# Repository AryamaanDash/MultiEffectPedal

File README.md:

# MultiEffectPedal

## Description

Multi-effect guitar pedal firmware and a custom KiCad PCB for the Daisy Seed.
The firmware runs distortion, stereo reverb, delay, and flanger effects at the
Daisy audio sample rate, with a footswitch for cycling through the effects.

## Firmware architecture

```text
src/main.cpp             Hardware composition and application entry point
src/AudioEngine.cpp      Real-time block processing and output limiting
src/EffectManager.cpp    Effect ownership-independent routing and mode changes
src/PedalControls.cpp    Foreground switch scanning and LED state
src/effects/             Individual DSP effect adapters
include/                 Public interfaces and shared audio types
```

Every effect implements the `EffectProcessor` interface:

```cpp
virtual void Init(float sample_rate) = 0;
virtual void SetParameters(const EffectParameters& parameters) = 0;
virtual StereoFrame Process(float input) = 0;
```

Effect parameters use normalized values from 0 to 1. Each adapter maps those
values to the range expected by its DaisySP processor. Mode changes are sent
from the foreground loop through an atomic request and applied by the audio
engine at the next block boundary.

The reverb and one-second delay buffers remain in external SDRAM. Effect
objects and the manager are statically allocated; audio processing performs no
dynamic allocation.

## Building

This project expects `libDaisy` and `DaisySP` to be available at the paths in
the `Makefile`.

```sh
make
```

To add an effect, implement `EffectProcessor`, register the instance with
`EffectManager`, and add its source file to `CPP_SOURCES` in the `Makefile`.

## Tools

- Daisy Seed and libDaisy
- DaisySP and DaisySP-LGPL
- KiCad PCB and schematic design

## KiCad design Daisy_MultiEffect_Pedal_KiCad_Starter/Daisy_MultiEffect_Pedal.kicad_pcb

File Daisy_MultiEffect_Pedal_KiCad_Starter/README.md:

# Daisy Seed Multi-Effect Guitar Pedal KiCad Starter

Files:
- Daisy_MultiEffect_Pedal.kicad_sch
- Daisy_MultiEffect_Pedal.kicad_pcb
- Daisy_MultiEffect_Pedal.kicad_pro

Important:
- This is a starter schematic/PCB template, not a production-ready board.
- Open in KiCad, verify every symbol, footprint, and pinout.
- Run ERC and DRC before fabrication.
- USB power is assumed for the prototype.
- Do not connect 9V, VIN, or 5V to Daisy ADC pins or +3V3A.
- Your current C++ writes mono to both output channels but this PCB routes only AUDIO OUT L to the mono output jack.
- RV5 is wired as a passive output volume control, so the single potentiometer does something with the current firmware.
- RV1-RV4 are optional future ADC control headers. Do not populate them unless you also update the firmware to read ADC values.

Key nets:
- D9_SWITCH: momentary footswitch to GND
- AUDIO_IN_L: buffered guitar input into Daisy audio input left
- AUDIO_OUT_L: Daisy audio output left into output buffer
- VREF_1V65: half-supply bias for the single-supply op-amp sections
- OUT_LEVEL_IN: AC-coupled signal into RV5 volume lug 3
- OUT_JACK_TIP: RV5 wiper to the output jack tip
- +3V3A: Daisy analog 3.3V rail
- GND: AGND and DGND tied together

Build wiring:
- Put the MCP6002 in an 8-pin DIP socket at U1. Pin 1 is the notched/dot end.
- Wire the input jack tip/sleeve to J1 pad 1/pad 2.
- Wire the output jack tip/sleeve to J2 pad 1/pad 2.
- Wire the momentary footswitch to SW1 pad 1 and pad 2.
- Wire the volume pot to RV5: pad 1 = CCW/GND, pad 2 = wiper/output, pad 3 = CW/input from output coupling capacitor.
- Mount RV1-RV4 only if you add ADC support in firmware later.

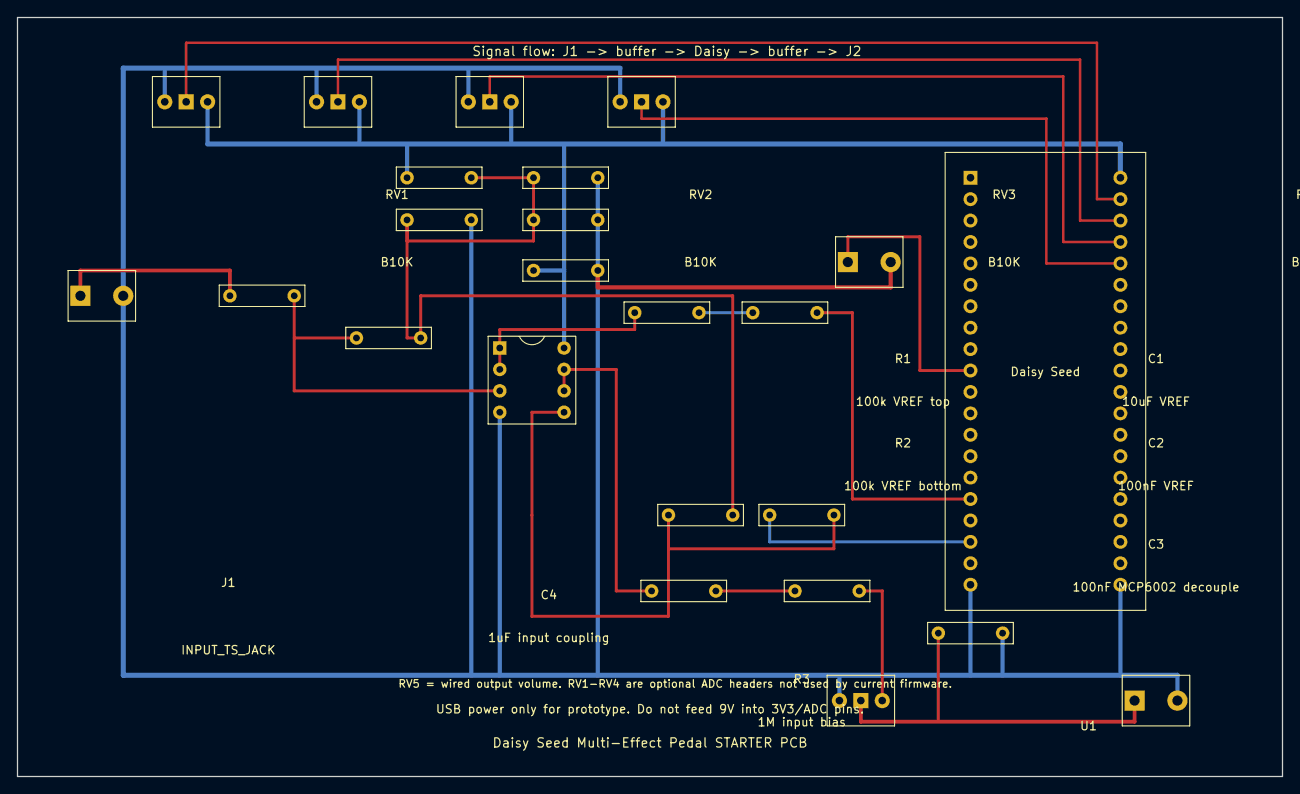
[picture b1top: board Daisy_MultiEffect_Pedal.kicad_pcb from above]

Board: 2 copper layers, 150.0 x 90.0 mm, 24 parts (0 on the bottom side), 19 nets.

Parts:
C1: 10uF VREF; TH_2Pin_7p62
C2: 100nF VREF; TH_2Pin_7p62
C3: 100nF MCP6002 decouple; TH_2Pin_7p62
C4: 1uF input coupling; TH_2Pin_7p62
C5: 1uF to Daisy In; TH_2Pin_7p62
C6: 1uF from Daisy Out; TH_2Pin_7p62
C7: 10uF output coupling; TH_2Pin_7p62
J1: INPUT_TS_JACK; Jack_or_Switch_2Pin
J2: OUTPUT_TS_JACK; Jack_or_Switch_2Pin
R1: 100k VREF top; TH_2Pin_7p62
R2: 100k VREF bottom; TH_2Pin_7p62
R3: 1M input bias; TH_2Pin_7p62
R4: 100R; TH_2Pin_7p62
R5: 100k out bias; TH_2Pin_7p62
R6: 100R out iso; TH_2Pin_7p62
R7: 100k output pulldown; TH_2Pin_7p62
RV1, RV2, RV3, RV4: B10K; Pot_3Pin_B10K_Wired
RV5: B10K volume; Pot_3Pin_B10K_Wired
SW1: MOMENTARY_MODE_SWITCH; Jack_or_Switch_2Pin
U1: MCP6002-I/P; DIP-8_W7.62mm
U2: Daisy Seed socket / 2x20; Daisy_Seed_2x20_Socket

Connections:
+3V3A: C3.1, R1.1, RV1.3 (CW/3V3A), RV2.3 (CW/3V3A), RV3.3 (CW/3V3A), RV4.3 (CW/3V3A), U1.8, U2.21 (PIN21)
AUDIO_IN_L: C5.2, U2.16 (PIN16)
AUDIO_OUT_L: C6.1, U2.18 (PIN18)
BUF_IN_OUT: R4.1, U1.1, U1.2
BUF_TO_DAISY_C: C5.1, R4.2
D9_SWITCH: SW1.1 (TIP/SW1), U2.10 (PIN10)
GND: C1.2, C2.2, C3.2, J1.2 (SLEEVE/SW2), J2.2 (SLEEVE/SW2), R2.2, R7.2, RV1.1 (CCW/GND), RV2.1 (CCW/GND), RV3.1 (CCW/GND), RV4.1 (CCW/GND), RV5.1 (CCW/GND), SW1.2 (SLEEVE/SW2), U1.4, U2.20 (PIN20), U2.40 (PIN40)
INPUT_NODE: C4.2, R3.1, U1.3
IN_JACK_TIP: C4.1, J1.1 (TIP/SW1)
OUT_BUF_INPUT: C6.2, R5.1, U1.5
OUT_BUF_OUT: R6.1, U1.6, U1.7
OUT_CAP_IN: C7.1, R6.2
OUT_JACK_TIP: J2.1 (TIP/SW1), R7.1, RV5.2 (WIPER)
OUT_LEVEL_IN: C7.2, RV5.3 (CW/LEVEL_IN)
POT1_A0_D15: RV1.2 (WIPER), U2.22 (PIN22)
POT2_A1_D16: RV2.2 (WIPER), U2.23 (PIN23)
POT3_A2_D17: RV3.2 (WIPER), U2.24 (PIN24)
POT4_A3_D18: RV4.2 (WIPER), U2.25 (PIN25)
VREF_1V65: C1.1, C2.1, R1.2, R2.1, R3.2, R5.2

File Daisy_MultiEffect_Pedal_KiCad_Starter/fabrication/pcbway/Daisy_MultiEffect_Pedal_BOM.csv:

"Refs","Value","Footprint","Qty","DNP"
"C1","10uF VREF bulk","Custom:TH_2Pin_7p62","1",""
"C2","100nF VREF bypass","Custom:TH_2Pin_7p62","1",""
"C3","100nF op-amp decouple","Custom:TH_2Pin_7p62","1",""
"C4","1uF input coupling","Custom:TH_2Pin_7p62","1",""
"C5","1uF into Daisy","Custom:TH_2Pin_7p62","1",""
"C6","1uF from Daisy Out","Custom:TH_2Pin_7p62","1",""
"C7","10uF final output coupling","Custom:TH_2Pin_7p62","1",""
"J1","Input TS jack: tip/sleeve","Custom:Jack_or_Switch_2Pin","1",""
"J2","Output TS jack: tip/sleeve","Custom:Jack_or_Switch_2Pin","1",""
"R1","100k VREF top","Custom:TH_2Pin_7p62","1",""
"R2","100k VREF bottom","Custom:TH_2Pin_7p62","1",""
"R3","1M to VREF","Custom:TH_2Pin_7p62","1",""
"R4","100R","Custom:TH_2Pin_7p62","1",""
"R5","100k output bias","Custom:TH_2Pin_7p62","1",""
"R6","100R output iso","Custom:TH_2Pin_7p62","1",""
"R7","100k pulldown","Custom:TH_2Pin_7p62","1",""
"RV1","B10K wet/dry","Custom:Pot_3Pin_B10K_Wired","1",""
"RV2","B10K amount","Custom:Pot_3Pin_B10K_Wired","1",""
"RV3","B10K time/rate","Custom:Pot_3Pin_B10K_Wired","1",""
"RV4","B10K feedback","Custom:Pot_3Pin_B10K_Wired","1",""
"RV5","B10K output level","Custom:Pot_3Pin_B10K_Wired","1",""
"SW1","Momentary mode switch","Custom:Jack_or_Switch_2Pin","1",""
"U1","MCP6002 dual op-amp","Package_DIP:DIP-8_W7.62mm","1",""
"U2","Daisy Seed minimal pinout","Custom:Daisy_Seed_2x20_Socket","1",""
